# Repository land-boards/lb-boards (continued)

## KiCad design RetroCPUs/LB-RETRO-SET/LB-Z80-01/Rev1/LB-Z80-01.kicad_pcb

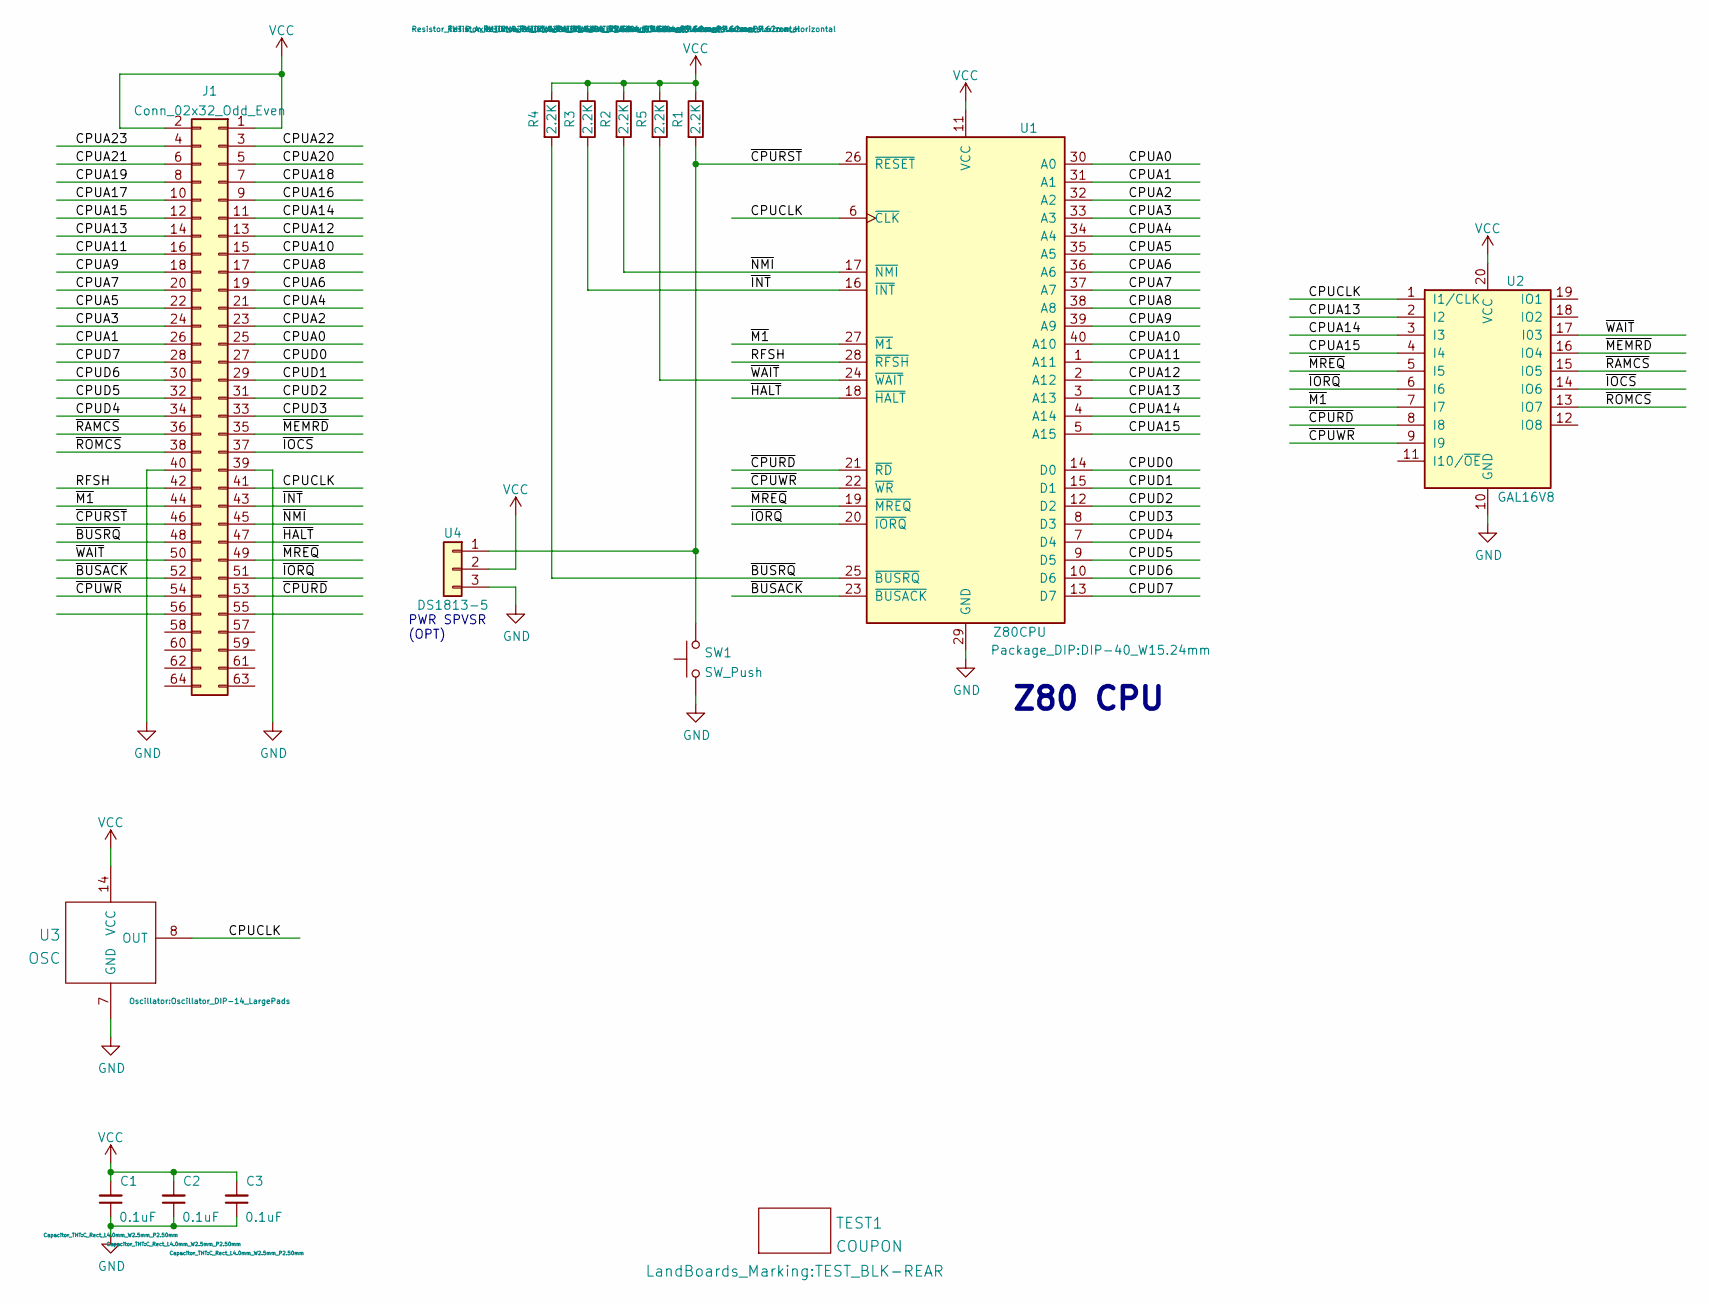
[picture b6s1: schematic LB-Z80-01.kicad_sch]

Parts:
C1, C2, C3: 0.1uF; C_Rect_L4.0mm_W2.5mm_P2.50mm
J1: Conn_02x32_Odd_Even; PinHeader_2x32_P2.54mm_Horizontal-FLIPPED
R1, R2, R3, R4, R5: 2.2K; R_Axial_DIN0204_L3.6mm_D1.6mm_P7.62mm_Horizontal
SW1: SW_Push; SW_PUSH_6mm_H8.5mm
TEST1: COUPON; TEST_BLK-REAR
U1: Z80CPU; DIP-40_W15.24mm
U2: GAL16V8; DIP-20_W7.62mm
U3: OSC; Oscillator_DIP-14_LargePads
U4: DS1813-5; TO-92

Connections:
/CPUA0: J1.25, U1.30 (A0)
/CPUA1: J1.26, U1.31 (A1)
/CPUA2: J1.23, U1.32 (A2)
/CPUA3: J1.24, U1.33 (A3)
/CPUA4: J1.21, U1.34 (A4)
/CPUA5: J1.22, U1.35 (A5)
/CPUA6: J1.19, U1.36 (A6)
/CPUA7: J1.20, U1.37 (A7)
/CPUA8: J1.17, U1.38 (A8)
/CPUA9: J1.18, U1.39 (A9)
/CPUA10: J1.15, U1.40 (A10)
/CPUA11: J1.16, U1.1 (A11)
/CPUA12: J1.13, U1.2 (A12)
/CPUA13: J1.14, U1.3 (A13), U2.2 (I2)
/CPUA14: J1.11, U1.4 (A14), U2.3 (I3)
/CPUA15: J1.12, U1.5 (A15), U2.4 (I4)
/CPUA16: J1.9
/CPUA17: J1.10
/CPUA18: J1.7
/CPUA19: J1.8
/CPUA20: J1.5
/CPUA21: J1.6
/CPUA22: J1.3
/CPUA23: J1.4
/CPUCLK: J1.41, U1.6 (~CLK), U2.1 (I1/CLK), U3.8 (OUT)
/CPUD0: J1.27, U1.14 (D0)
/CPUD1: J1.29, U1.15 (D1)
/CPUD2: J1.31, U1.12 (D2)
/CPUD3: J1.33, U1.8 (D3)
/CPUD4: J1.34, U1.7 (D4)
/CPUD5: J1.32, U1.9 (D5)
/CPUD6: J1.30, U1.10 (D6)
/CPUD7: J1.28, U1.13 (D7)
/RFSH: J1.42, U1.28 (~RFSH)
/~BUSACK: J1.52, U1.23 (~BUSACK)
/~BUSRQ: J1.48, R4.2, U1.25 (~BUSRQ)
/~CPURD: J1.53, U1.21 (~RD), U2.8 (I8)
/~CPURST: J1.46, R1.2, SW1.2, U1.26 (~RESET), U4.1
/~CPUWR: J1.54, U1.22 (~WR), U2.9 (I9)
/~HALT: J1.47, U1.18 (~HALT)
/~INT: J1.43, R3.2, U1.16 (~INT)
/~IOCS: J1.37, U2.14 (IO6)
/~IORQ: J1.51, U1.20 (~IORQ), U2.6 (I6)
/~M1: J1.44, U1.27 (~M1), U2.7 (I7)
/~MEMRD: J1.35, U2.16 (IO4)
/~MREQ: J1.49, U1.19 (~MREQ), U2.5 (I5)
/~NMI: J1.45, R2.2, U1.17 (~NMI)
/~RAMCS: J1.36, U2.15 (IO5)
/~ROMCS: J1.38, U2.13 (IO7)
/~WAIT: J1.50, R5.2, U1.24 (~WAIT), U2.17 (I03)
GND: C1.1, C2.1, C3.1, J1.39, J1.40, SW1.1, U1.29 (GND), U2.10 (GND), U3.7 (GND), U4.3
VCC: C1.2, C2.2, C3.2, J1.1, J1.2, R1.1, R2.1, R3.1, R4.1, R5.1, U1.11 (VCC), U2.20 (VCC), U3.14 (VCC), U4.2

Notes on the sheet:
Z80 CPU
PWR SPVSR (OPT)

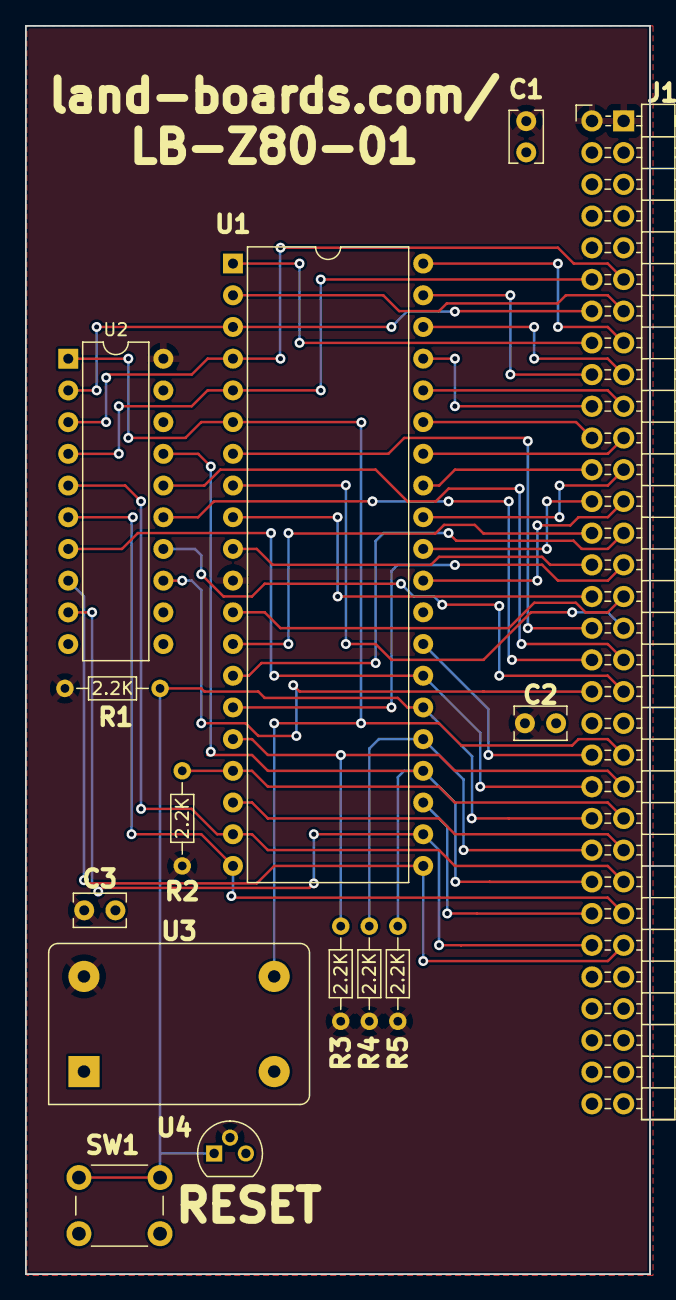
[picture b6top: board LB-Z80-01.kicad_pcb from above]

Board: 2 copper layers, 50.0 x 100.0 mm, 15 parts (0 on the bottom side), 44 nets.

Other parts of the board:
TEST: COUPON; TEST_BLK-REAR
